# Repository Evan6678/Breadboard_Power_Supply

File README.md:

# Breadboard Power Supply (Through-Hole Edition)

A simple and solder-friendly breadboard power supply designed in KiCad. This board takes a 9 V input from a barrel jack and provides a regulated 5 V or 3.3 V output through jumper-selectable headers and screw terminals. It is built entirely with through-hole components so it is easy to assemble, troubleshoot, and practice soldering on a real PCB.

This project is part of my ongoing work to learn KiCad, electronics fundamentals, and the full workflow of designing and building PCBs from scratch. It serves as my starting point for future hardware projects that will build on these skills.

---

## Features

* 9 V input via DC barrel jack
* On-board power switch and P-channel MOSFET high-side gating
* Linear regulation using the LM7805 and LM317
* Jumper selection for 5 V or 3.3 V output
* Output available on both breadboard header pins and screw terminals
* Supports 500 mA continuous current (thermal limits of linear regulators apply)
* Designed entirely with through-hole components for easy assembly
* Clear schematic and board layout suitable for beginners learning KiCad and basic EE

---

## Project Motivation

I created this board to build confidence in schematic capture, PCB layout, and hardware design decisions. My short-term goal is to design functional and realistic boards, and my long-term goal is to develop repeatable workflows that will let me design my own hardware products.

This first version uses through-hole components to make soldering and prototyping accessible. A future branch of this project will use only SMD components for a smaller footprint and a more polished power supply module for personal use in upcoming electronics projects.

---

## Repository Contents

* Full KiCad project files
* PDF schematic
* PDF board layout sheet
* 3D through-hole model render
* Notes and revision history for future SMD version

---

## Schematic

[Schematic PDF](ReadmeResources/BreadBoardPowerSupplySchematic.pdf)

---

## PCB Layout

[PCB Layout PDF](ReadmeResources/BreadBoardPowerSupplyThroghHolePCB.pdf)

---

## 3D Model (Through-Hole Build)

---

## Output Options

The board includes:

* Jumper-selectable 5 V or 3.3 V supply
* Breadboard header pins for fast prototyping
* Screw terminals for powering external circuits
* Status LED indicators for each rail
* Filtering capacitors for stable linear regulation
* Reverse-current protection on each regulated output

In the schematic, each regulator block is shown with its filtering capacitors, protection diodes, jumper header wiring, and LED indicators.

---

## Future Plans

This project will continue to evolve as I learn:

* SMD-only redesign for a more compact footprint
* Improved layout and routing strategies
* Switching regulator upgrades to increase efficiency
* Higher current output and thermal improvements
* Custom enclosures and accessory boards for personal projects

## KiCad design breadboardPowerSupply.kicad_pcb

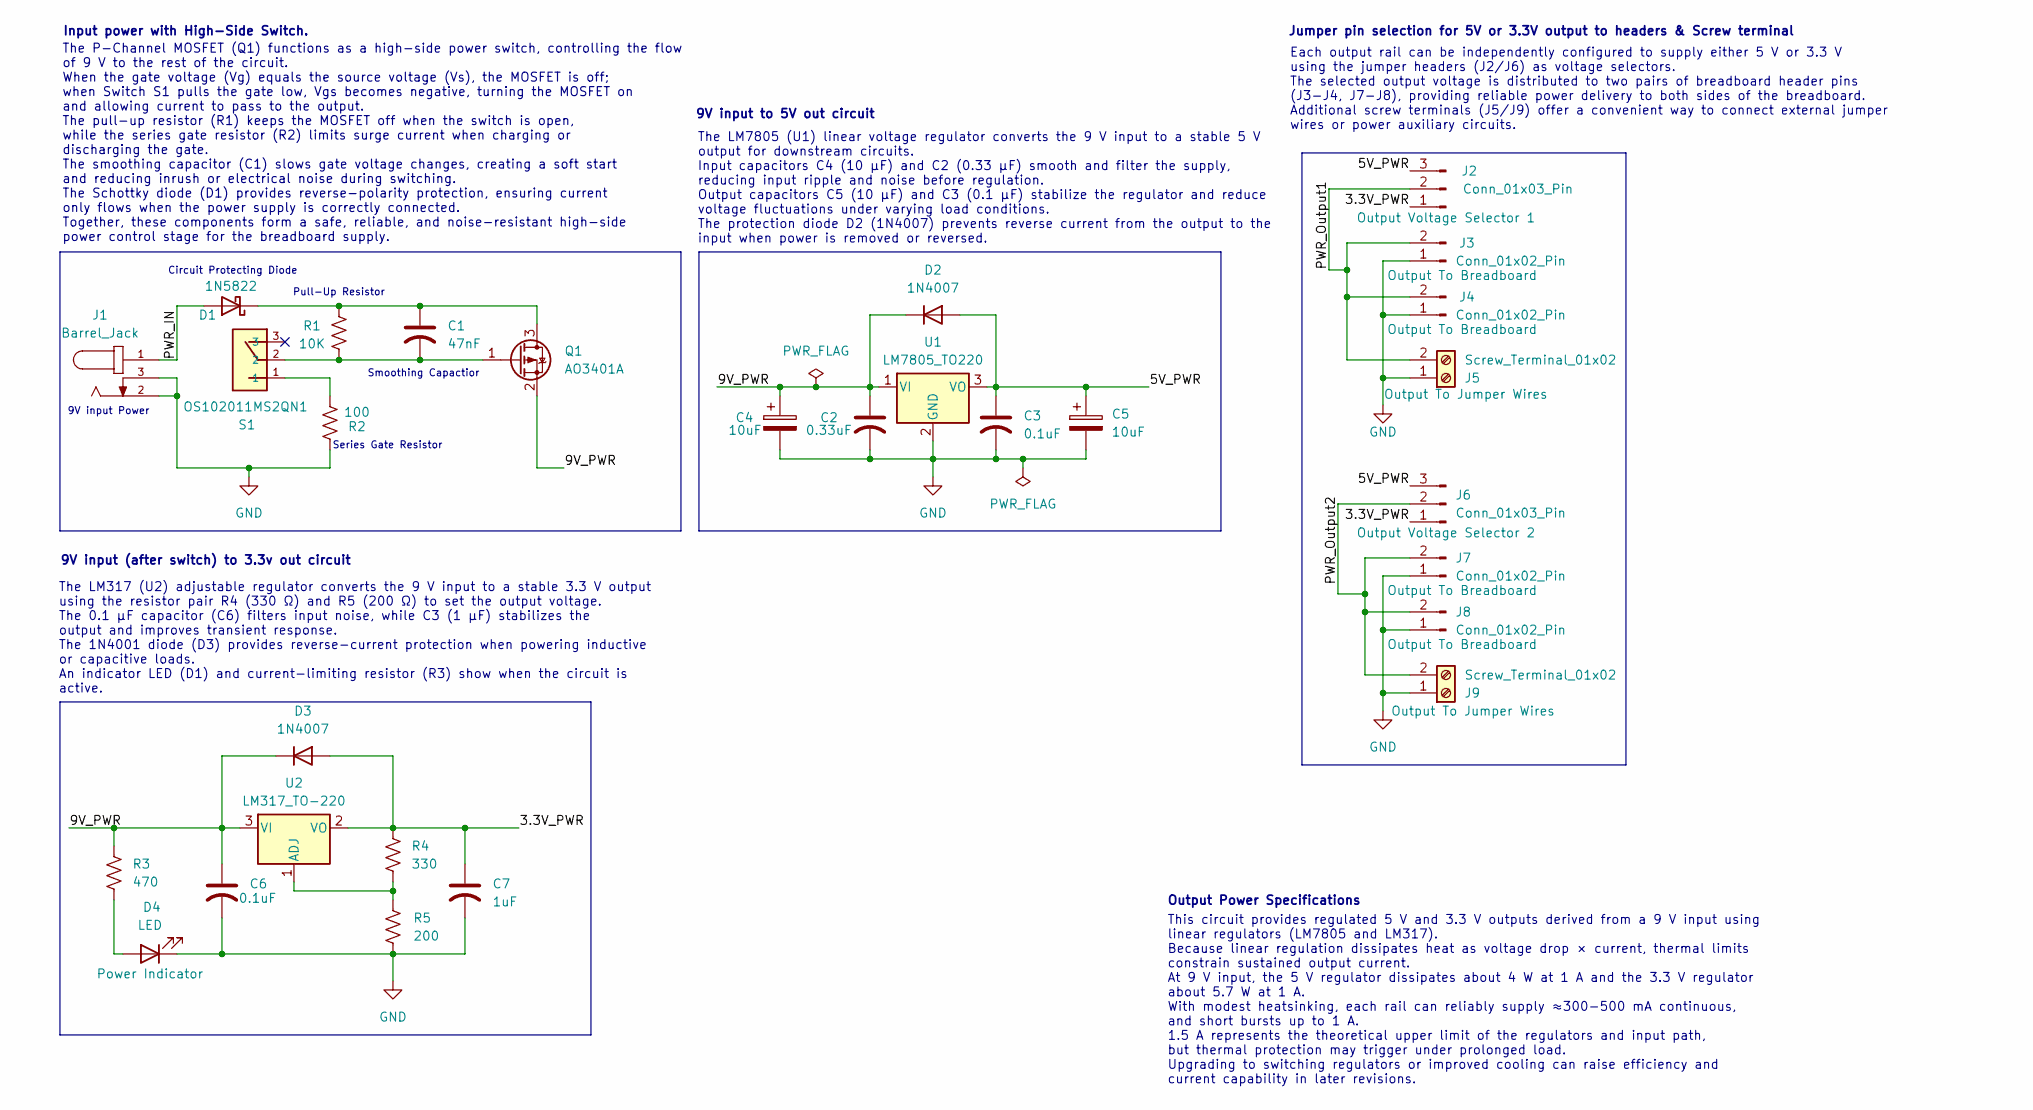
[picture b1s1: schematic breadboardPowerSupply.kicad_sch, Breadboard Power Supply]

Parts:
C1: 47nF; C_Disc_D3.0mm_W1.6mm_P2.50mm
C2: 0.33uF; C_Disc_D3.0mm_W1.6mm_P2.50mm
C3, C6: 0.1uF; C_Disc_D3.0mm_W1.6mm_P2.50mm
C4, C5: 10uF; C_Radial_D5.0mm_H11.0mm_P2.00mm
C7: 1uF; C_Disc_D3.0mm_W1.6mm_P2.50mm
D1: 1N5822; D_A-405_P10.16mm_Horizontal
D2, D3: 1N4007; D_DO-41_SOD81_P10.16mm_Horizontal
D4: LED; LED_D5.0mm
J1: Barrel_Jack; CUI_PJ-002A
J2, J6: Conn_01x03_Pin; PinHeader_1x03_P2.54mm_Vertical
J3, J4, J7, J8: Conn_01x02_Pin; PinHeader_1x02_P2.54mm_Vertical
J5, J9: Screw_Terminal_01x02; TerminalBlock_Xinya_XY308-2.54-2P_1x02_P2.54mm_Horizontal
Q1: AO3401A; SOT-23
R1: 10K; R_Axial_DIN0204_L3.6mm_D1.6mm_P7.62mm_Horizontal
R2: 100; R_Axial_DIN0204_L3.6mm_D1.6mm_P7.62mm_Horizontal
R3: 470; R_Axial_DIN0204_L3.6mm_D1.6mm_P7.62mm_Horizontal
R4: 330; R_Axial_DIN0204_L3.6mm_D1.6mm_P7.62mm_Horizontal
R5: 200; R_Axial_DIN0204_L3.6mm_D1.6mm_P7.62mm_Horizontal
S1: OS102011MS2QN1; SW_Slide_SS12F44_SPDT
U1: LM7805_TO220; TO-220-3_Vertical
U2: LM317_TO-220; TO-220-3_Vertical

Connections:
/3.3V_PWR: C7.1, D3.2 (A), J2.1, J6.1, R4.2, U2.2 (VO)
/5V_PWR: C3.1, C5.1, D2.2 (A), J2.3, J6.3, U1.3 (VO)
/9V_PWR: C2.1, C4.1, C6.1, D2.1 (K), D3.1 (K), Q1.2 (S), R3.2, U1.1 (VI), U2.3 (VI)
/PWR_IN: D1.2 (A), J1.1
/PWR_Output1: J2.2, J3.2, J4.2, J5.2
/PWR_Output2: J6.2, J7.2, J8.2, J9.2
GND: C2.2, C3.2, C4.2, C5.2, C6.2, C7.2, D4.1 (K), J1.2, J1.3, J3.1, J4.1, J5.1, J7.1, J8.1, J9.1, R2.2, R5.1, U1.2 (GND)
unnamed: C1.1, D1.1 (K), Q1.3 (D), R1.2
unnamed: D4.2 (A), R3.1
unnamed: C1.2, Q1.1 (G), R1.1, S1.2
unnamed: R2.1, S1.1
unnamed: R4.1, R5.2, U2.1 (ADJ)

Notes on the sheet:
Circuit Protecting Diode
Pull-Up Resistor
Input power with High-Side Switch.
Jumper pin selection for 5V or 3.3V output to headers & Screw terminal
Output Power Specifications
This circuit provides regulated 5 V and 3.3 V outputs derived from a 9 V input using linear regulators (LM7805 and LM317). Because linear regulation dissipates heat as voltage drop × current, thermal limits constrain sustained output current. At 9 V input, the 5 V regulator dissipates about 4 W at 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
The P-Channel MOSFET (Q1) functions as a high-side power switch, controlling the flow of 9 V to the rest of the circuit. When the gate voltage (Vg) equals the source voltage (Vs), the MOSFET is off; when Switch S1 pulls the gate low, Vgs becomes negative, turning the MOSFET on and allowing current 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
9V input Power
Series Gate Resistor
Smoothing Capactior
The LM317 (U2) adjustable regulator converts the 9 V input to a stable 3.3 V output using the resistor pair R4 (330 Ω) and R5 (200 Ω) to set the output voltage. The 0.1 µF capacitor (C6) filters input noise, while C3 (1 µF) stabilizes the output and improves transient response. The 1N4001 diode (D3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
The LM7805 (U1) linear voltage regulator converts the 9 V input to a stable 5 V output for downstream circuits. Input capacitors C4 (10 µF) and C2 (0.33 µF) smooth and filter the supply, reducing input ripple and noise before regulation. Output capacitors C5 (10 µF) and C3 (0.1 µF) stabilize the re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
9V input to 5V out circuit
Each output rail can be independently configured to supply either 5 V or 3.3 V using the jumper headers (J2/J6) as voltage selectors. The selected output voltage is distributed to two pairs of breadboard header pins (J3-J4, J7-J8), providing reliable power delivery to both sides of the breadboard. 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
9V input (after switch) to 3.3v out circuit

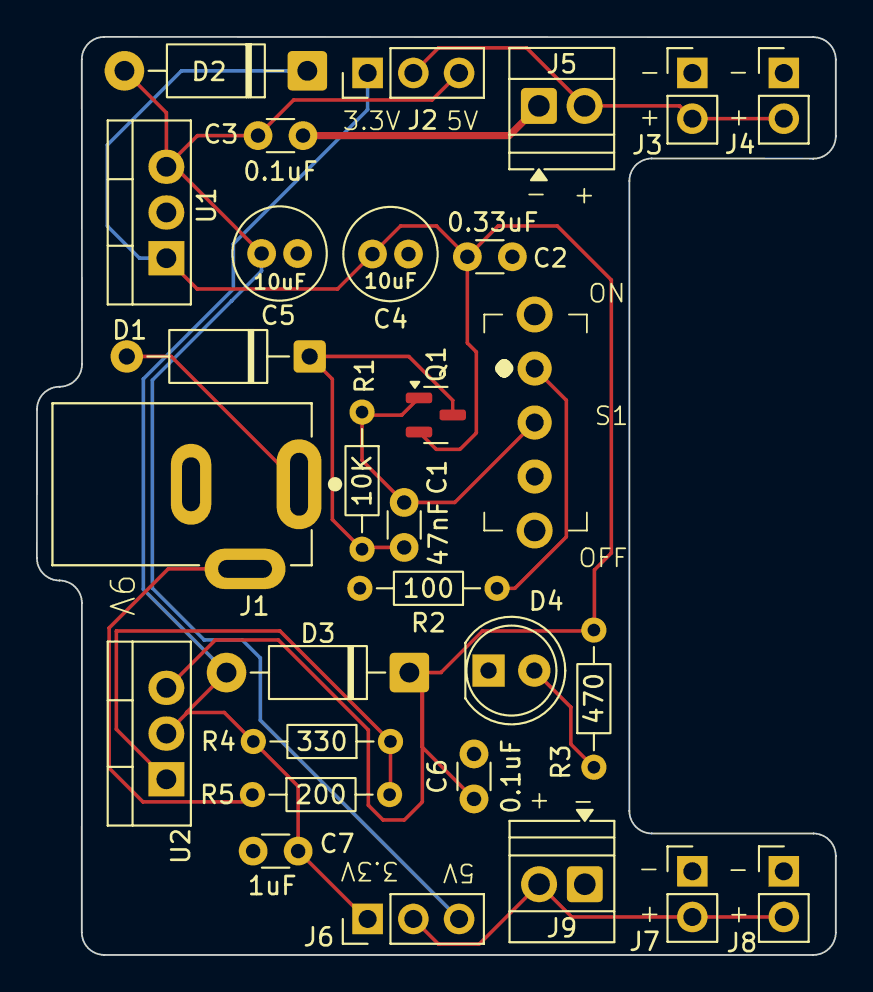
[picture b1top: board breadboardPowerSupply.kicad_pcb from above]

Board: 2 copper layers, 44.4 x 51.0 mm, 29 parts (0 on the bottom side), 12 nets.

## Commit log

2025-11-28 Add project Readme
